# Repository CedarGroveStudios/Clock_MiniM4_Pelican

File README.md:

# Clock_MiniM4_Pelican (Clock Minima)
## _A minimal but large clock in a Pelican 1040 Micro Case with CircuitPython_

The Clock_MiniM4 is an RTC-based minimal LED display clock implementation inspired by John Park's MetroMinimalist Clock design. The clock uses custom CircuitPython libraries __CedarGroveStudios/Unit_Converter__ for automatic Daylight Saving Time (DTS) and __CedarGroveStudios/Clock_Builder__ for display and user interface functions.

Caution: Under elevated temperature conditions, the sealed Pelican case may not sufficiently dissipate the heat from the clock electronics. A test of the internal operating temperature measured 80F (27C) when interior room temperature was nominally 77F (25C). If the clock will be operated in warmer environments, it is recommended that some holes be drilled into the case to allow air flow.

Photo 1. During assembly.

Photo 2. Test of auxilliary day-of-week display.

<a href="https://oshpark.com/shared_projects/Iv0tE7jk"></img></a>

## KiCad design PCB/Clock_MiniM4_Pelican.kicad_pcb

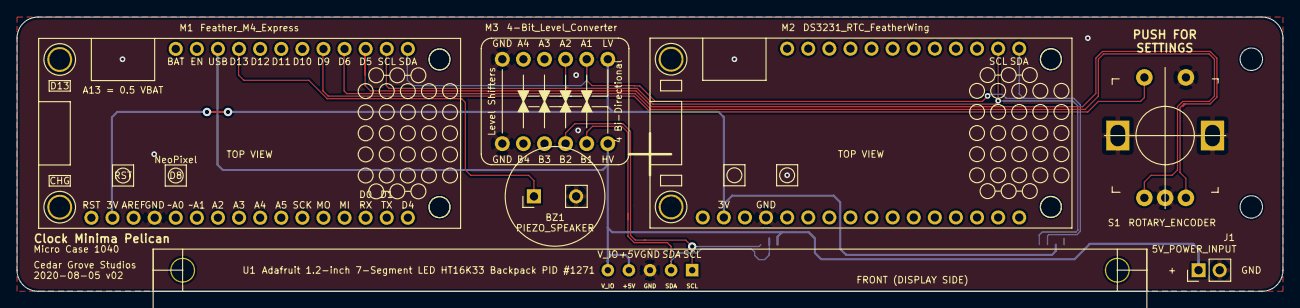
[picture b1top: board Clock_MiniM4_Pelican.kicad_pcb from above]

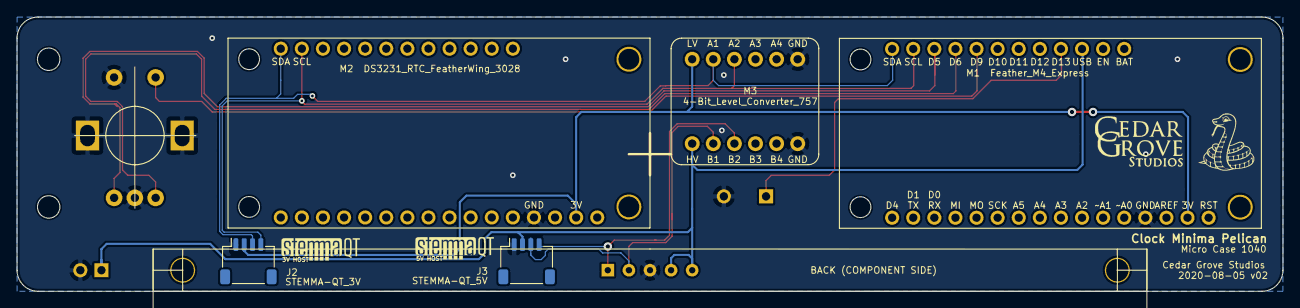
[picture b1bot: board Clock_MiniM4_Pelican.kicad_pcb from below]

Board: 2 copper layers, 152.4 x 33.0 mm, 10 parts (2 on the bottom side), 11 nets.

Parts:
BZ1: PIEZO_SPEAKER; Socket_Strip_Straight_1x02_Pitch2.54mm
J1: 5V_POWER_INPUT; PinHeader_1x02_P2.54mm_Vertical
J2: STEMMA-QT_3V; JST_SH_SM04B-SRSS-TB_1x04-1MP_P1.00mm_Horizontal
J3: STEMMA-QT_5V; JST_SH_SM04B-SRSS-TB_1x04-1MP_P1.00mm_Horizontal
J**: 2.1mm_THT_DC_panel_power_conn_610
M1: Feather_M4_Express; Adafruit_Feather_M4_Express
M2: DS3231_RTC_FeatherWing; Adafruit_Feather_M4_Express
M3: 4-Bit_Level_Converter; 4-Bit_Level_Converter_757
S1: ROTARY_ENCODER; Rotary_Encoder_Switched_PEC11R_mntg_hole
U1: 1.2-inch_7-segment_LED_HT16K33_backpack

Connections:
+3V3: J2.2, M1.2, M2.2, M3.1
/5V_SCL: J3.4, M3.10, U1.1
/5V_SDA: J3.3, M3.11, U1.2
/D5: M1.26, S1.B
/D6: M1.25, S1.A
/D9: M1.24, S1.1
/D13-LED: BZ1.1, M1.20
/SCL: J2.4, M1.27, M2.27, M3.3
/SDA: J2.3, M1.28, M2.28, M3.2
/USB: J1.1, J3.2, M1.19, M3.12, U1.4, U1.5
GND: BZ1.2, J1.2, J2.1, J3.1, M1.4, M2.4, M3.6, M3.7, S1.2, S1.3, S1.C, U1.3

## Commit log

2020-06-01 initial repo load
2020-06-02 update PCB design
2020-06-04 update schematic drawing
2020-06-18 update BOM
2020-06-22 update photos
2020-07-05 remove pybadge code
2020-07-06 update RTC fail alert process
2020-07-06 update for configuration file
2020-07-06 update image with clockbuilder changes
2020-07-19 update graphics
2020-07-25 update PCB; display bright in param file
2020-07-26 update CPy 5.3 image folder
2020-07-26 update CPy 5.3 image and BOM
2020-08-02 add day-of-week clock code
2020-08-05 Update new PCB design - fix STEMMA-QT pinout
2020-08-07 update pcb
2020-08-07 include day-of-week test photo
2020-11-09 Image updated with corrected unit_converter.chronos library (fixes delayed DST)
2020-12-06 Update fp-info-cache
2021-01-17 update/remove photos
2021-07-12 update documentation
2022-09-02 update license
2022-12-15 update docs
2023-09-16 update image folder
